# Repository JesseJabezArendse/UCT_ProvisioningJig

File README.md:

# UCT Provisioning Jig

This repository contains all resources and guides for the UCT Provisioning Jig.

---

### [Raspberry Pi Code/](https://github.com/JesseJabezArendse/UCT_ProvisioningJig/tree/main/Raspberry%20Pi%20Code)
This directory contains the main source code for the Provisioning Jig. 
It includes python scripts for hardware interaction and device programming.

### [PCBs/](https://github.com/JesseJabezArendse/UCT_ProvisioningJig/tree/main/PCB)
Schematics and PCB layouts for the Provisioning Jig and UCT Debugger v2.1.

### [Enclosure/](https://github.com/JesseJabezArendse/UCT_ProvisioningJig/tree/main/Enclosure)
Solidworks files, gcode and Assembly Guidelines for the Enclosure of the Provisioning Jig.

### [Documentation](https://github.com/JesseJabezArendse/UCT_ProvisioningJig/tree/main/Provisioning%20Jig%20v3%20Documentation.pdf)
Guidelines and specifications for using and modifying the Provisioning Jig.

---

## How to use the Provisioning Jig

1. Write the ProvisioningJig_V2J45.IMG file onto a 16GB SD Card using [Win32DiskImager](https://win32diskimager.org/).
2. 3D print the enclosure using the provided [gcode files](https://github.com/JesseJabezArendse/UCT_ProvisioningJig/tree/main/Enclosure/Enclosure%20gcode) and assemble according to the [guide](https://github.com/JesseJabezArendse/UCT_ProvisioningJig/blob/main/Enclosure/Assembly%20Guide.docx).

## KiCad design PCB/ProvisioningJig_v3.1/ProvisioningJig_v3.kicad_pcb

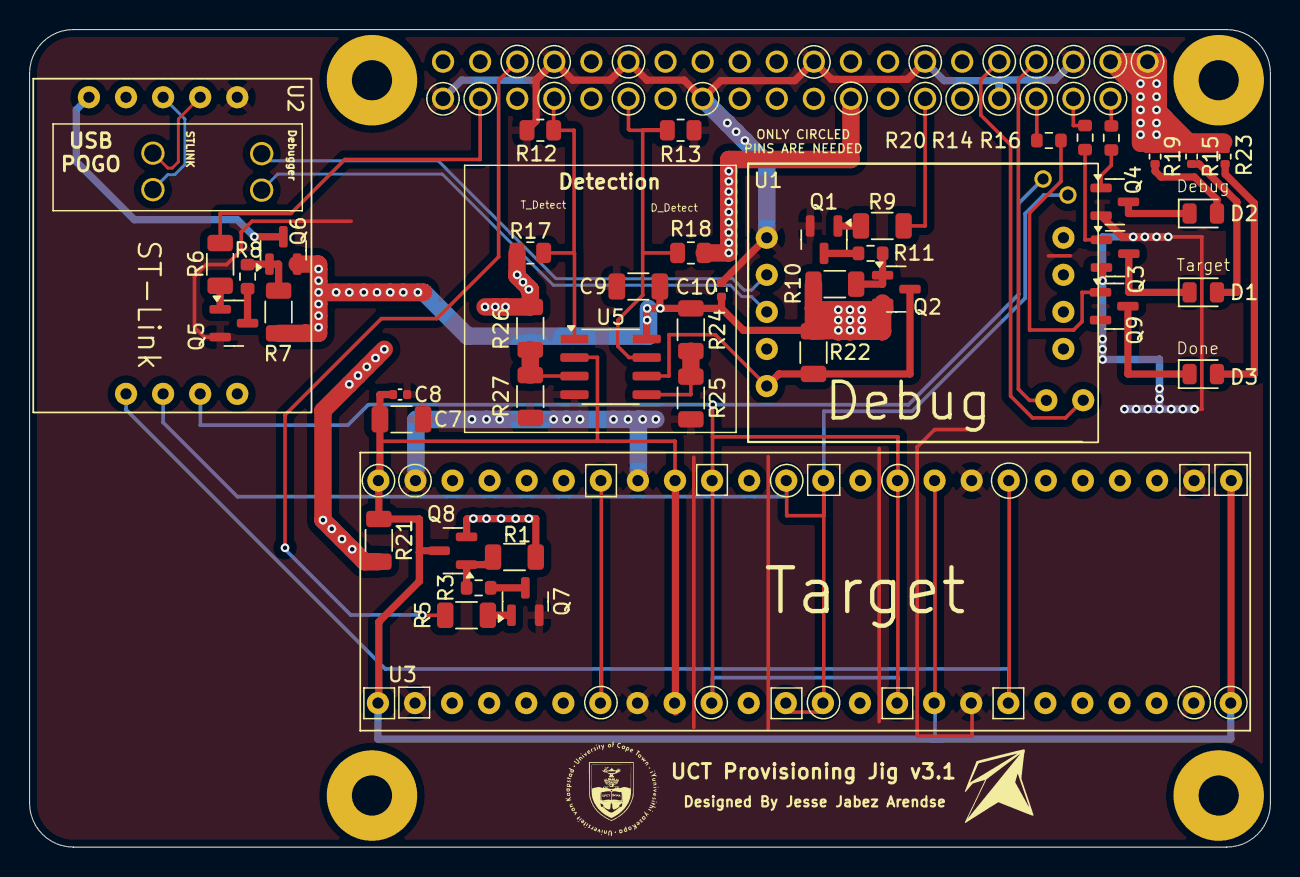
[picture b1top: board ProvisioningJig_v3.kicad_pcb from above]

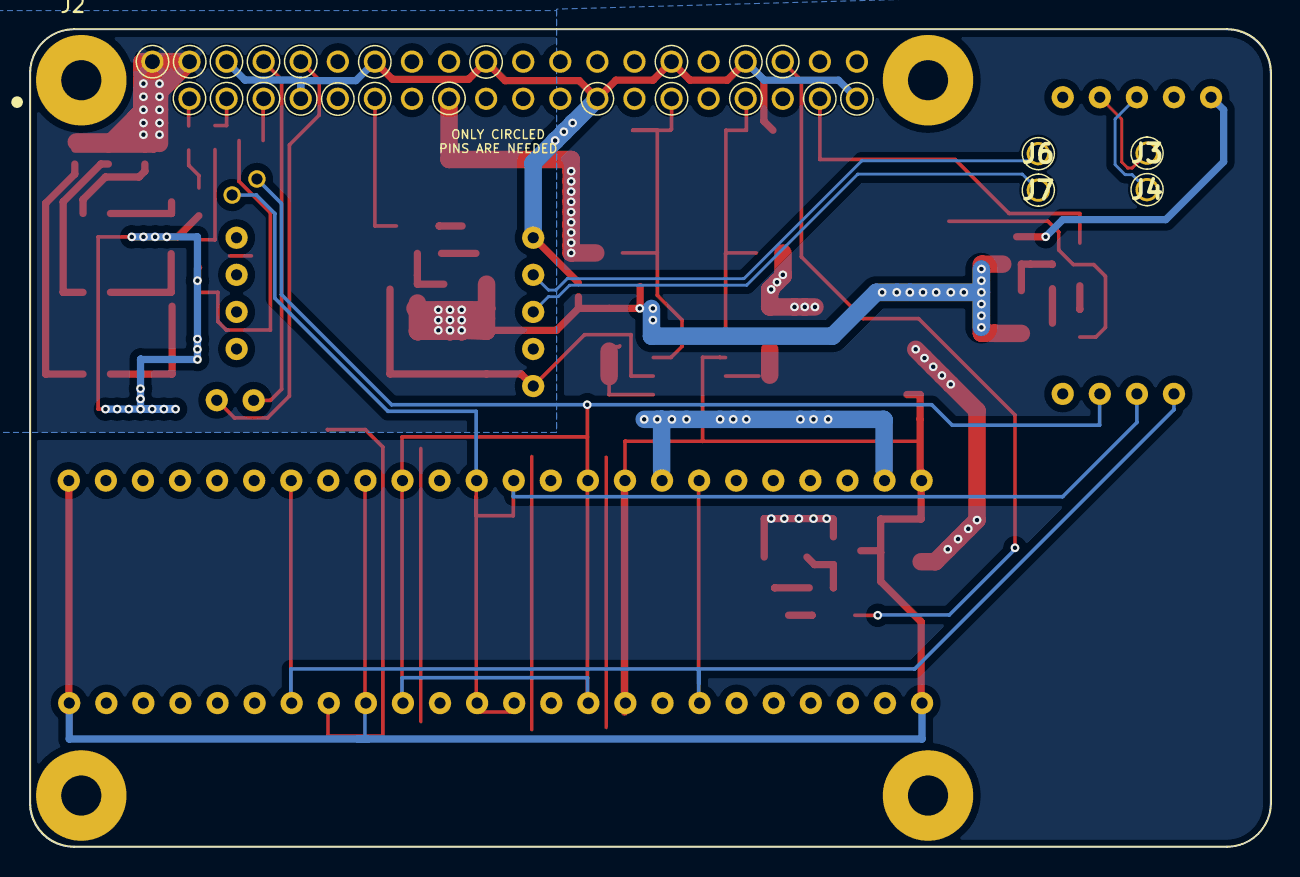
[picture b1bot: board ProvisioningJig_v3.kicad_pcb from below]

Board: 2 copper layers, 85.0 x 56.0 mm, 50 parts (5 on the bottom side), 43 nets.

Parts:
C7, C9: 100u; C_1206_3216Metric
C8, C10: 100n; C_0402_1005Metric
D1, D2: Yellow; D_0805_2012Metric
D3: Green; D_0805_2012Metric
J2: Raspberry_Pi_2_3; RASPBERRY_PI_3B
J3: POGO USB1+; P702200045
J4: POGO USB1-; P702200045
J6: POGO USB2+; P702200045
J7: POGO USB2-; P702200045
Q1, Q3, Q4, Q5, Q7, Q9: S8050_SMD; SOT-23
Q2, Q6, Q8: AO3401A; SOT-23
R1, R5, R6, R7, R9, R10, R21, R22, R24, R25, R26, R27: 100k; R_1206_3216Metric
R3, R8, R11, R14, R16, R20: 1k; R_0603_1608Metric
R12, R13, R17, R18: 10k; R_0805_2012Metric
R15, R19, R23: 100; R_0402_1005Metric
U1: New Version Debugger; STLINK_UCT
U2: ST-Link; STLINK_UCT
U3: Target; STM32F051C6T6
U5: LM393; SOIC-8-1EP_3.9x4.9mm_P1.27mm_EP2.29x3mm

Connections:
+3V3: J2.17 (3V3), Q8.2 (S), R1.1, R17.2, R18.2, R21.1, R26.1
+5V: C9.1, C10.1, J2.2 (5V), J2.4 (5V), Q2.2 (S), Q6.2 (S), R7.1, R10.1, R15.2, R19.2, R22.1, R23.2, R24.1, U5.8 (V+)
/D_Det_Bias: R24.2, R25.1, U5.5 (+)
/D_SWCLK: U1.11 (TP2), U2.7 (T_SWCLK), U3.12 (PA2), U3.13 (PA3), U3.36 (PF7), U3.37 (PA14)
/D_SWIO: U1.10 (TP1), U2.8 (T_SWDIO), U3.10 (PA0), U3.15 (PA5), U3.34 (PA13), U3.39 (PB3)
/Debug_Detect: J2.29 (GCLK1/GPIO5), R13.2, R18.1, U5.7
/Debugger_PWR: Q2.3 (D), R22.2, U1.1 (5V_USB), U5.6 (-)
/NRST: U2.6 (T_NRST), U3.7 (NRST), U3.18 (PB0), U3.31 (PA10), U3.42 (PB6)
/RPI_Debug_EN: J2.13 (GPIO27), R9.1
/RPI_STLINK_EN: J2.37 (GPIO26), R6.1
/RPI_Target_EN: J2.36 (GPIO16), R5.1
/Raspberry Pi IOs/D_Yellow: J2.3 (SDA/GPIO2), R16.1
/Raspberry Pi IOs/Green: J2.7 (GCLK0/GPIO4), R20.1
/Raspberry Pi IOs/T_Yellow: J2.5 (SCL/GPIO3), R14.1
/STLink_PWR: Q6.3 (D), U2.1 (5V_USB)
/STLink_Rx: J2.8 (GPIO14/TXD), U1.12 (Rx)
/STLink_Tx: J2.10 (GPIO15/RXD), U1.13 (Tx)
/T_Det_Bias: R26.2, R27.1, U5.3 (+)
/Target_Detect: J2.33 (PWM1/GPIO13), R12.2, R17.1, U5.1
/Target_PWR: C7.1, C8.1, Q8.3 (D), R21.2, U3.1 (VBAT), U3.9 (V+), U3.16 (PA6), U3.24 (V+), U3.25 (PB12), U3.33 (PA12), U3.40 (PB4), U3.48 (V+), U5.2 (-)
/USB1+: J3.1, U2.4 (USB_DP)
/USB1-: J4.1, U2.3 (USB_DM)
/USB2+: J6.1, U1.4 (USB_DP)
/USB2-: J7.1, U1.3 (USB_DM)
GND: C7.2, C8.2, C9.2, C10.2, J2.6 (GND), J2.9 (GND), J2.14 (GND), J2.20 (GND), J2.25 (GND), J2.30 (GND), J2.34 (GND), J2.39 (GND), Q1.2 (E), Q3.2 (E), Q4.2 (E), Q5.2 (E), Q7.2 (E), Q9.2 (E), R12.1, R13.1, R25.2, R27.2, U1.5 (GND), U2.5 (GND), U3.2 (PC13), U3.8 (GND), U3.17 (PA7), U3.23 (GND), U3.26 (PB13), U3.32 (PA11), U3.41 (PB5), U3.47 (GND), U5.4 (V-)
unnamed: D1.2 (A), R15.1
unnamed: D1.1 (K), Q3.3 (C)
unnamed: D2.2 (A), R19.1
unnamed: D2.1 (K), Q4.3 (C)
unnamed: D3.2 (A), R23.1
unnamed: D3.1 (K), Q9.3 (C)
unnamed: Q1.1 (B), R9.2
unnamed: Q1.3 (C), R11.1
unnamed: Q2.1 (G), R10.2, R11.2
unnamed: Q3.1 (B), R14.2
unnamed: Q4.1 (B), R16.2
unnamed: Q5.1 (B), R6.2
unnamed: Q5.3 (C), R8.1
unnamed: Q6.1 (G), R7.2, R8.2
unnamed: Q7.1 (B), R5.2
unnamed: Q7.3 (C), R3.1
unnamed: Q8.1 (G), R1.2, R3.2
unnamed: Q9.1 (B), R20.2

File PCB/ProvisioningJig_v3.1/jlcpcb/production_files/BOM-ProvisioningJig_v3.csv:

Comment,Designator,Footprint,LCSC,Quantity
100u,"C7,C9",C_1206_3216Metric,C15008,2
AO3401A,"Q2,Q6,Q8",SOT-23,C15127,3
10k,"R12,R13,R17,R18",R_0805_2012Metric,C17414,4
100k,"R1,R10,R21,R22,R24,R25,R26,R27,R5,R6,R7,R9",R_1206_3216Metric,C17900,12
1k,"R11,R14,R16,R20,R3,R8",R_0603_1608Metric,C21190,6
S8050_SMD,"Q1,Q3,Q4,Q5,Q7,Q9",SOT-23,C2146,6
Yellow,"D1,D2",D_0805_2012Metric,C2296,2
Green,D3,D_0805_2012Metric,C2297,1
100,"R15,R19,R2,R23,R4",R_0402_1005Metric,C25076,5
100n,"C10,C8",C_0402_1005Metric,C307331,2
Target Button,"SW1,SW2",SW_SPST_TL3342,C318884,2
USB for Debugger,"J1,J5",USB_Conn_JLC_LCSC_C404969,C404969,2
LM393,U5,SOIC-8-1EP_3.9x4.9mm_P1.27mm_EP2.29x3mm,C7955,1
Target,U3,STM32F051C6T6,,1
New Version Debugger,U1,STLINK_UCT,,1
ST-Link,U2,STLINK_UCT,,1
POGO USB2-,J7,P702200045,,1
POGO USB2+,J6,P702200045,,1
POGO USB1-,J4,P702200045,,1
POGO USB1+,J3,P702200045,,1
Raspberry_Pi_2_3,J2,RASPBERRY_PI_3B,,1

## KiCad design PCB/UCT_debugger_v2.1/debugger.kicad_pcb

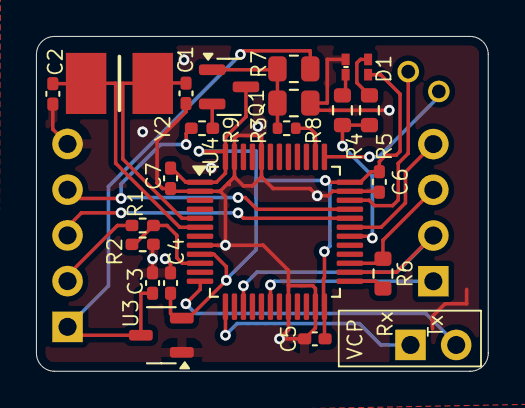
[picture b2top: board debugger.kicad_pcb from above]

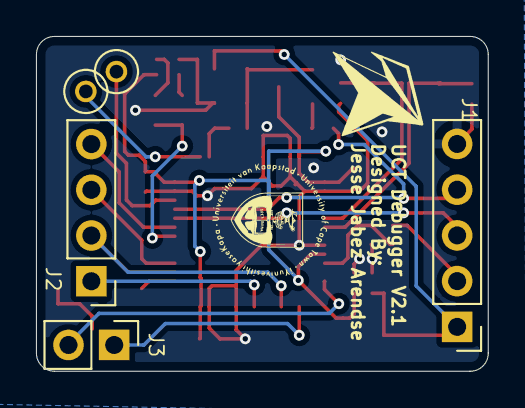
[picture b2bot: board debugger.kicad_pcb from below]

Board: 2 copper layers, 25.1 x 18.6 mm, 26 parts (5 on the bottom side), 24 nets.

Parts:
C1, C2: 10p; C_0402_1005Metric_Pad0.74x0.62mm_HandSolder
C3, C4: 1u; C_0402_1005Metric_Pad0.74x0.62mm_HandSolder
C5, C6, C7: 100n; C_0402_1005Metric_Pad0.74x0.62mm_HandSolder
D1: LED_Dual_AKAK; DUAL_LED_COM_CATH_0606
J1: Conn_01x05_Pin; PinHeader_1x05_P2.54mm_Vertical
J2: Conn_01x04_Pin; PinHeader_1x04_P2.54mm_Vertical
J3: Conn_01x02_Pin; PinHeader_1x02_P2.54mm_Vertical
Q1: S8050_SMD; SOT-23
R1, R9: 1k5; R_0402_1005Metric_Pad0.72x0.64mm_HandSolder
R2: 2k; R_0402_1005Metric_Pad0.72x0.64mm_HandSolder
R3: 100; R_0402_1005Metric
R4, R5, R6: 150R; R_0603_1608Metric
R7, R8: 10k; R_0805_2012Metric
TP1, TP2: TestPoint; TestPoint_Pad_D2.0mm
U3: XC6206PxxxMR; SOT-23-3
U4: STM32F103CBTx; LQFP-48_7x7mm_P0.5mm
Y2: X50328MSB2GI; RESC5032X135N

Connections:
+3V3: C4.1, C5.1, C6.1, C7.1, D1.1 (A1), Q1.3 (C), U3.2 (VO), U4.1 (VBAT), U4.9 (VDDA), U4.24 (VDD), U4.36 (VDD), U4.48 (VDD)
+5V: C3.1, J1.1, R7.2, U3.3 (VI)
/D_SWCLK: TP2.1, U4.37 (PA14)
/D_SWDIO: TP1.1, U4.34 (PA13)
/LED_STLINK: R4.2, R5.1, U4.30 (PA9)
/STLink_Rx: J3.1, U4.13 (PA3)
/STLink_Tx: J3.2, U4.12 (PA2)
/T_RST: J2.1, U4.18 (PB0)
/T_SWCLK: J2.2, U4.15 (PA5), U4.26 (PB13)
/T_SWDIO: J2.3, R6.1, U4.27 (PB14)
/T_SWO: J2.4, U4.31 (PA10)
/T_Voltage: J1.2, R1.1
/USB_DM: J1.3, U4.32 (PA11)
/USB_DP: J1.4, R9.2, U4.33 (PA12)
/USB_re_enum: R3.2, U4.38 (PA15)
GND: C1.2, C2.2, C3.2, C4.2, C5.2, C6.2, C7.2, D1.4 (K2), J1.5, R2.1, R8.1, U3.1 (GND), U4.2 (PC13), U4.8 (VSSA), U4.20 (PB2), U4.23 (VSS), U4.35 (VSS), U4.44 (BOOT0), U4.47 (VSS)
unnamed: D1.3 (A2), R5.2
unnamed: D1.2 (K1), R4.1
unnamed: Q1.1 (B), R3.1, R7.1, R8.2
unnamed: Q1.2 (E), R9.1
unnamed: R1.2, R2.2, U4.10 (PA0)
unnamed: R6.2, U4.25 (PB12)
unnamed: C1.1, U4.5 (PD0), Y2.1
unnamed: C2.1, U4.6 (PD1), Y2.2

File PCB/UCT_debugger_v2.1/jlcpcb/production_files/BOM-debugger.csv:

Comment,Designator,Footprint,LCSC
X50328MSB2GI,Y2,RESC5032X135N,C115962
100n,"C5,C6,C7",C_0402_1005Metric_Pad0.74x0.62mm_HandSolder,C1525
10k,"R7,R8",R_0805_2012Metric,C17414
S8050_SMD,Q1,SOT-23,C2146
150R,"R4,R5,R6",R_0603_1608Metric,C22808
100,R3,R_0402_1005Metric,C25076
1k5,"R1,R9",R_0402_1005Metric_Pad0.72x0.64mm_HandSolder,C25867
LED_Dual_AKAK,D1,DUAL_LED_COM_CATH_0606,C2827309
10p,"C1,C2",C_0402_1005Metric_Pad0.74x0.62mm_HandSolder,C32949
2k,R2,R_0402_1005Metric_Pad0.72x0.64mm_HandSolder,C4109
1u,"C3,C4",C_0402_1005Metric_Pad0.74x0.62mm_HandSolder,C52923
XC6206PxxxMR,U3,SOT-23-3,C5446
STM32F103CBTx,U4,LQFP-48_7x7mm_P0.5mm,C8304

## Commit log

2025-01-05 added directories
    folders for each component of the jig
2025-01-05 Added RPI Code
    RPI Code
2025-01-06 added raspberry pi code
2025-01-06 modified provisioning jig code
2025-01-06 final push
2025-01-12 fixed target slot
